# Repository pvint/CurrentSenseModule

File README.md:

# CurrentSenseModule
An I2C DC Current Sense Module based on a TI INA220 IC

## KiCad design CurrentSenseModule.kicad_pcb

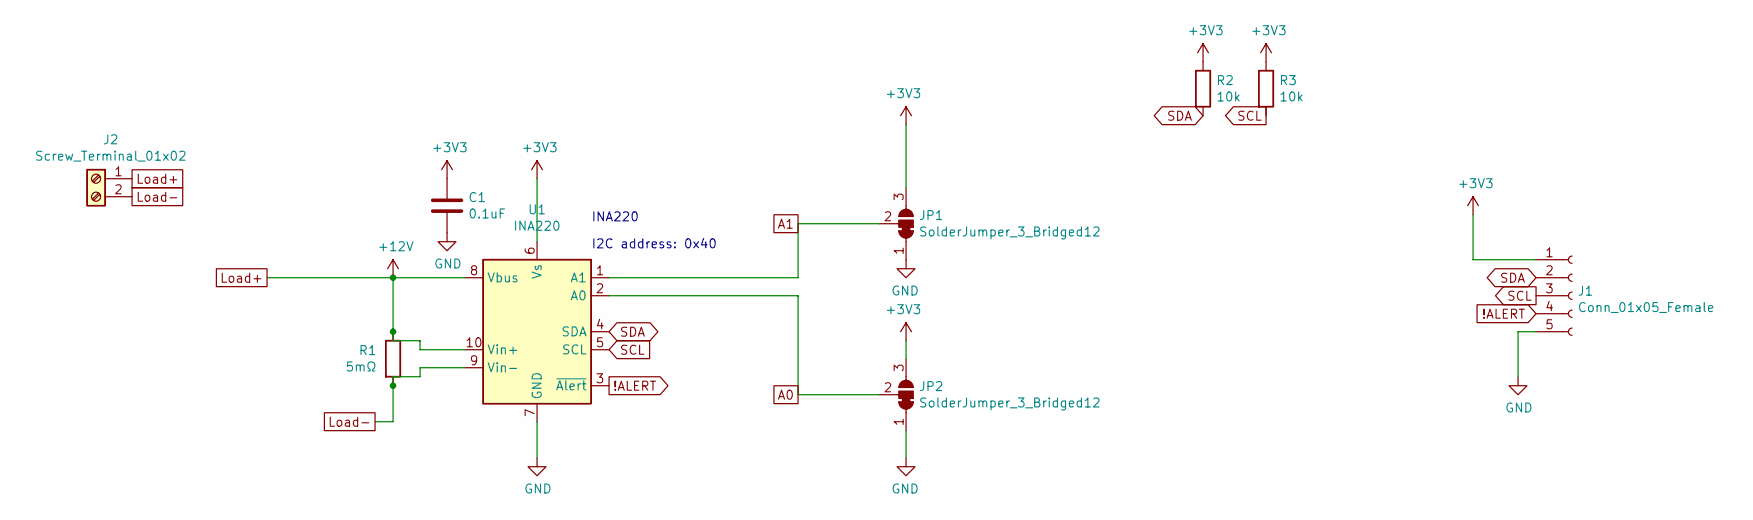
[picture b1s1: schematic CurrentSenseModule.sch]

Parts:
C1: 0.1uF; C_0805_2012Metric
J1: Conn_01x05_Female; PinHeader_1x05_P2.54mm_Vertical
J2: Screw_Terminal_01x02; Term_Block_1x2_P5mm
JP1, JP2: SolderJumper_3_Bridged12; SolderJumper-3_P1.3mm_Bridged2Bar12_RoundedPad1.0x1.5mm_Num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
R1: 5mΩ; R_1206_3216Metric
R2, R3: 10k; R_0805_2012Metric
U1: INA220; MSOP-10_3x3mm_P0.5mm

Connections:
!ALERT: J1.4, U1.3 (~Alert~)
+3V3: C1.1, J1.1, JP1.3 (B), JP2.3 (B), R2.1, R3.1, U1.6 (Vs)
A0: JP2.2 (C), U1.2 (A0)
A1: JP1.2 (C), U1.1 (A1)
GND: C1.2, J1.5, JP1.1 (A), JP2.1 (A), U1.7 (GND)
Load+: J2.1, R1.1, U1.8 (Vbus), U1.10 (Vin+)
Load-: J2.2, R1.2, U1.9 (Vin-)
SCL: J1.3, R3.2, U1.5 (SCL)
SDA: J1.2, R2.2, U1.4 (SDA)

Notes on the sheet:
I2C address: 0x40
INA220

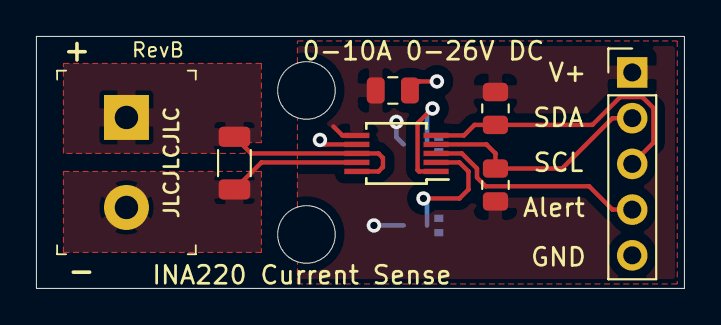
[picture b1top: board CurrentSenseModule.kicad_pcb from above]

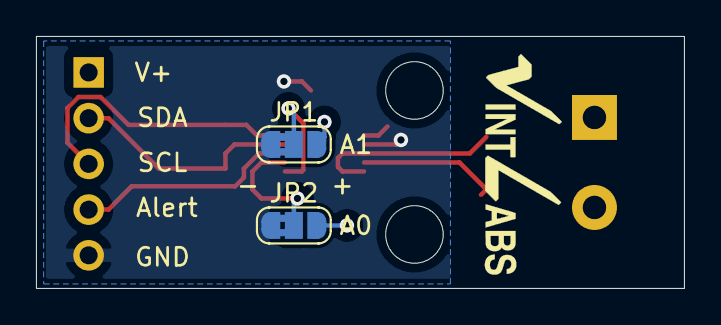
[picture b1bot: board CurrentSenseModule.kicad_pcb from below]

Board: 2 copper layers, 36.0 x 14.0 mm, 9 parts (2 on the bottom side), 9 nets.

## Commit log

2021-11-12 Initial Import (RevB)
2022-01-30 Added schematic PDF
